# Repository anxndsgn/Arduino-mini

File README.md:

# Arduino-mini

The Minimum Arduino board, based on ATmega328P.

The size is 21*21mm.

The 0.1 version is on [EasyEDA](https://oshwhub.com/camcyano/arduinomini).

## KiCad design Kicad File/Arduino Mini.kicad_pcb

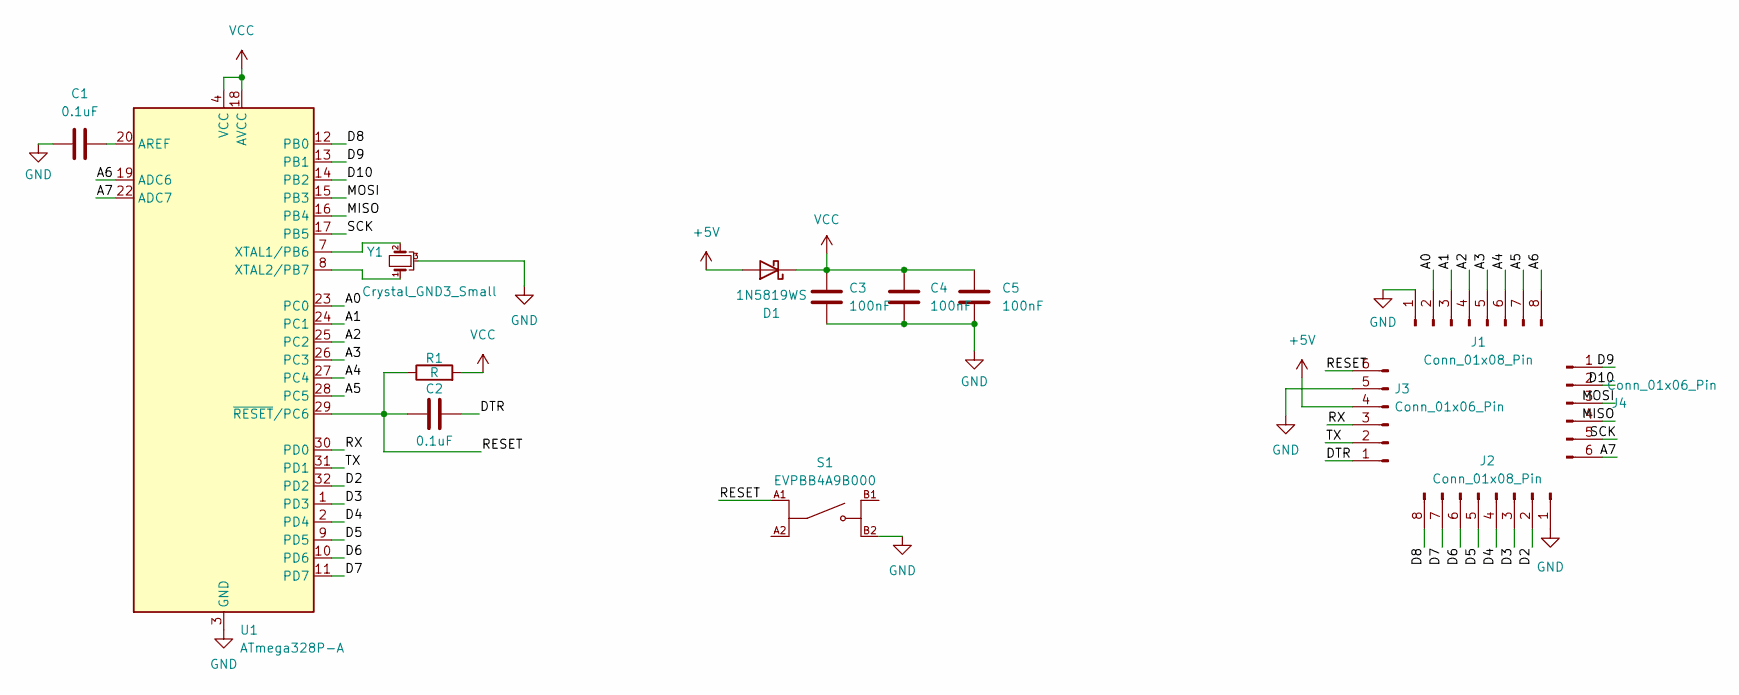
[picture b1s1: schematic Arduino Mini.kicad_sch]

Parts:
C1, C2: 0.1uF; C_0805_2012Metric
C3, C4, C5: 100nF; C_0805_2012Metric
D1: 1N5819WS; D_SOD-323
J1, J2: Conn_01x08_Pin; PinHeader_1x08_P2.54mm_Vertical
J3, J4: Conn_01x06_Pin; PinHeader_1x06_P2.54mm_Vertical
R1: R; R_0805_2012Metric
S1: EVPBB4A9B000; SW_EVPBB4A9B000; DIGI-KEY_PART_NUMBER P19888CT-ND
U1: ATmega328P-A; TQFP-32_7x7mm_P0.8mm
Y1: Crystal_GND3_Small; Resonator_SMD_Murata_CSTxExxV-3Pin_3.0x1.1mm

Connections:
+5V: D1.2 (A), J3.4
/A0: J1.2, U1.23 (PC0)
/A1: J1.3, U1.24 (PC1)
/A2: J1.4, U1.25 (PC2)
/A3: J1.5, U1.26 (PC3)
/A4: J1.6, U1.27 (PC4)
/A5: J1.7, U1.28 (PC5)
/A6: J1.8, U1.19 (ADC6)
/A7: J4.6, U1.22 (ADC7)
/D2: J2.2, U1.32 (PD2)
/D3: J2.3, U1.1 (PD3)
/D4: J2.4, U1.2 (PD4)
/D5: J2.5, U1.9 (PD5)
/D6: J2.6, U1.10 (PD6)
/D7: J2.7, U1.11 (PD7)
/D8: J2.8, U1.12 (PB0)
/D9: J4.1, U1.13 (PB1)
/D10: J4.2, U1.14 (PB2)
/DTR: C2.2, J3.1
/MISO: J4.4, U1.16 (PB4)
/MOSI: J4.3, U1.15 (PB3)
/RESET: C2.1, J3.6, R1.1, S1.A1, U1.29 (~RESET/PC6)
/RX: J3.3, U1.30 (PD0)
/SCK: J4.5, U1.17 (PB5)
/TX: J3.2, U1.31 (PD1)
GND: C1.1, C3.2, C4.2, C5.2, J1.1, J2.1, J3.5, S1.B2, U1.3 (GND), U1.5 (GND), U1.21 (GND), Y1.3
unnamed: C1.2, U1.20 (AREF)
unnamed: U1.7 (XTAL1/PB6), Y1.2
unnamed: U1.8 (XTAL2/PB7), Y1.1
VCC: C3.1, C4.1, C5.1, D1.1 (K), R1.2, U1.4 (VCC), U1.6 (VCC), U1.18 (AVCC)

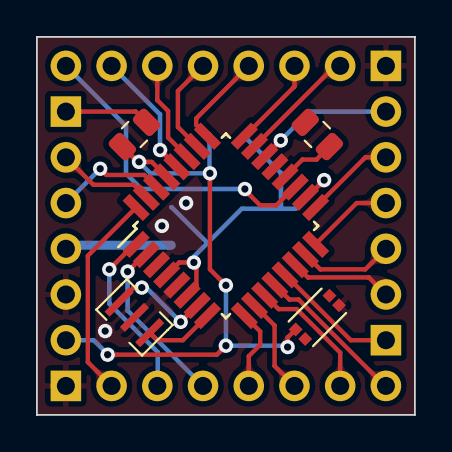
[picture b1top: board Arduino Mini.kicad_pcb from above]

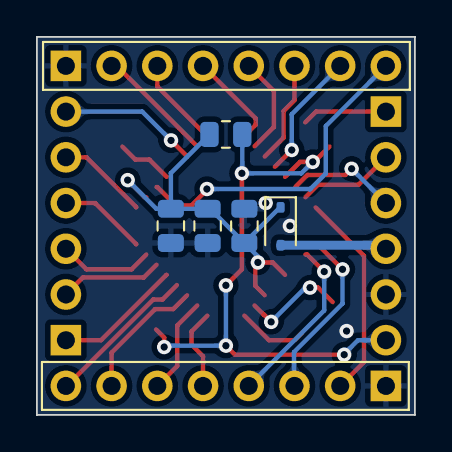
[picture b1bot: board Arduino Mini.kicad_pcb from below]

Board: 2 copper layers, 21.0 x 21.0 mm, 14 parts (9 on the bottom side), 30 nets.

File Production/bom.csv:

Designator,Footprint,Quantity,Value,LCSC Part #
"C1, C2",0805,2,0.1uF,
"C3, C4, C5",0805,3,100nF,
D1,D_SOD-323,1,1N5819WS,
"J1, J2",PinHeader_1x08_P2.54mm_Vertical,2,Conn_01x08_Pin,
"J3, J4",PinHeader_1x06_P2.54mm_Vertical,2,Conn_01x06_Pin,
R1,0805,1,R,
S1,SW_EVPBB4A9B000,1,EVPBB4A9B000,
U1,TQFP-32_7x7mm_P0.8mm,1,ATmega328P-A,
Y1,Resonator_SMD_Murata_CSTxExxV-3Pin_3.0x1.1mm,1,Crystal_GND3_Small,

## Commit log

2023-10-17 Create LICENSE
2023-10-17 create kicad file
2023-10-18 add kicad file
2023-10-18 update pcb
2023-10-18 add Gerber
2023-10-18 add sch

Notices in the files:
Kicad File/Arduino Mini.kicad_sch:
MIT License
